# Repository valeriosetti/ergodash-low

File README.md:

# What's this?

I've worked the ErgoDash keyboard for a while and it felt quite good, but it was a bit too
high for me. So I decided to design my own version in order to make it thinner.
Here's what I did:

- have all switches PCB mounted.
- do not use acrylic frame and let the PCB sit directly on the desktop.
- use low profile Gateron switches (KS-27).

In addition:

- I also added some holes at the corners of the board in order to make it
tiltable/adjustable with some screw.
- I replaced some of the pinky keys with 2u keycaps because my pinky's accuracy
is not really great.

## Kicad preview

## Picture of the assembled board

# What's next?

I've been using this keyboard for more than a year now and I find it really
comfortable. There are still some improvements I would like to try though:

- make a new version with Kailh choch v1 keys in order to see if I can make
it even thinner than this.
- improve keys' position and perhaps also reduce the overall number:
    - central keys are not easily reachable with the index finger, so they
      might be lowered a bit in the layout.
    - 4 keys in the low-left row are too much (I currently have 2 Win-keys +
      Ctrl + Alt), so they can be reduced.

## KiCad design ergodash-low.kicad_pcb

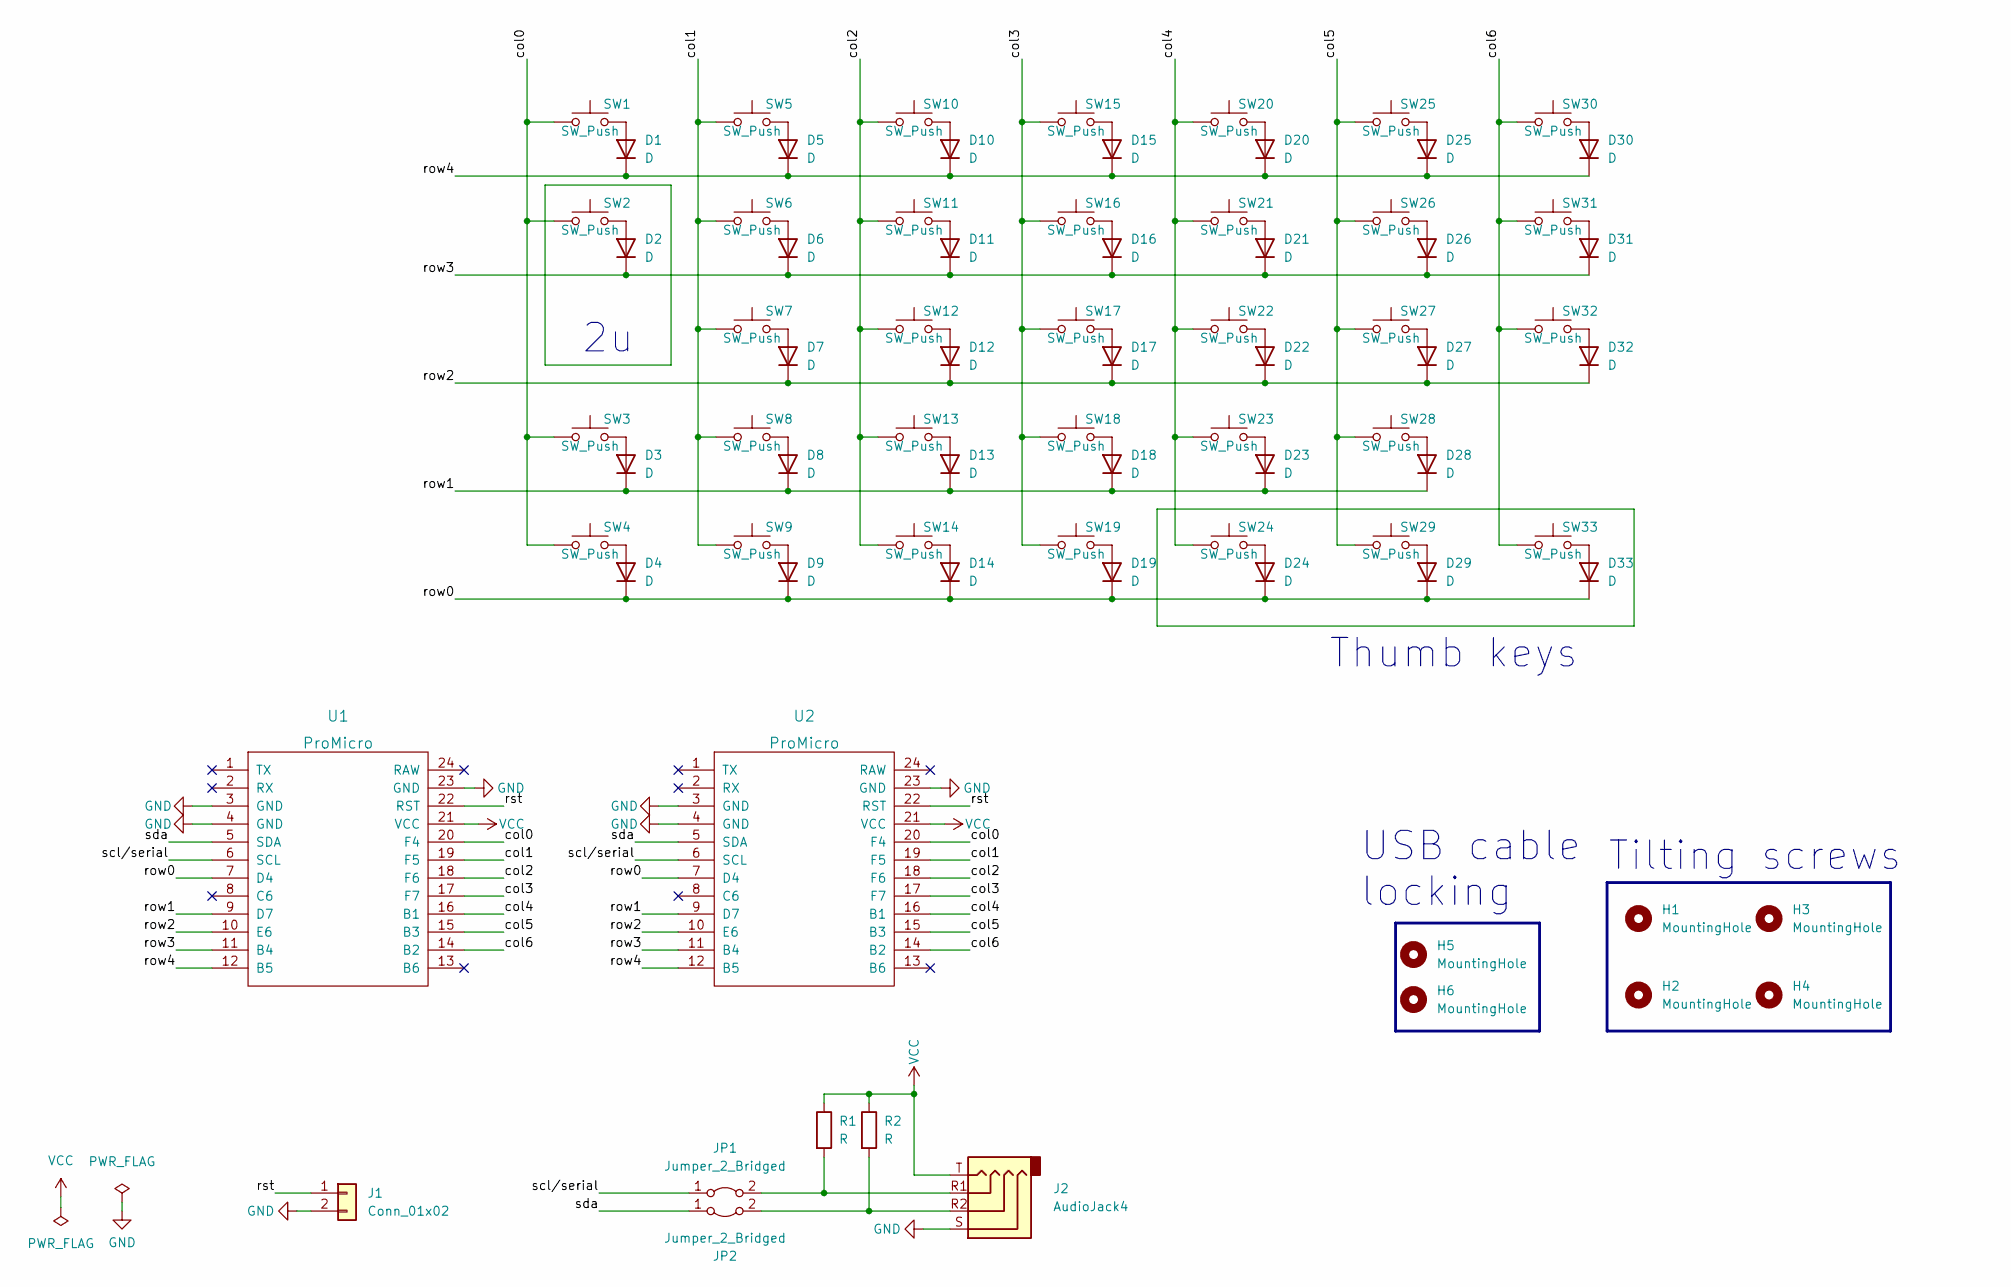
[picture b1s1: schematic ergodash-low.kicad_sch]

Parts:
D1, D2, D3, D4, D5, D6, D7, D8, D9, D10, D11, D12, D13, D14, D15, D16, D17, D18, D19, D20, D21, D22, D23, D24, D25, D26, D27, D28, D29, D30, D31, D32, D33: D; D_SOD-123-reversible
H1, H2, H3, H4: MountingHole; MountingHole_5.3mm_M5
H5, H6: MountingHole; MountingHole_4mm
J1: Conn_01x02; PinHeader_1x02_P2.54mm_Vertical
J2: AudioJack4; TRRS-PJ-320A-dual
JP1, JP2: Jumper_2_Bridged; SolderJumper-2_P1.3mm_Bridged_RoundedPad1.0x1.5mm
R1, R2: R; R_0603_1608Metric_Pad0.98x0.95mm_HandSolder
SW1, SW3, SW4, SW5, SW6, SW7, SW8, SW9, SW10, SW11, SW12, SW13, SW14, SW15, SW16, SW17, SW18, SW19, SW20, SW21, SW22, SW23, SW24, SW25, SW26, SW27, SW28, SW30, SW31, SW32: SW_Push; gateron_ks27_reversible
SW2, SW29, SW33: SW_Push; gateron_ks27_reversible_stabilizer
U1, U2: ProMicro

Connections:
/col0: SW1.1, SW2.1, SW3.1, SW4.1, U1.20 (F4), U2.20 (F4)
/col1: SW5.1, SW6.1, SW7.1, SW8.1, SW9.1, U1.19 (F5), U2.19 (F5)
/col2: SW10.1, SW11.1, SW12.1, SW13.1, SW14.1, U1.18 (F6), U2.18 (F6)
/col3: SW15.1, SW16.1, SW17.1, SW18.1, SW19.1, U1.17 (F7), U2.17 (F7)
/col4: SW20.1, SW21.1, SW22.1, SW23.1, SW24.1, U1.16 (B1), U2.16 (B1)
/col5: SW25.1, SW26.1, SW27.1, SW28.1, SW29.1, U1.15 (B3), U2.15 (B3)
/col6: SW30.1, SW31.1, SW32.1, SW33.1, U1.14 (B2), U2.14 (B2)
/row0: D4.1 (K), D9.1 (K), D14.1 (K), D19.1 (K), D24.1 (K), D29.1 (K), D33.1 (K), U1.7 (D4), U2.7 (D4)
/row1: D3.1 (K), D8.1 (K), D13.1 (K), D18.1 (K), D23.1 (K), D28.1 (K), U1.9 (D7), U2.9 (D7)
/row2: D7.1 (K), D12.1 (K), D17.1 (K), D22.1 (K), D27.1 (K), D32.1 (K), U1.10 (E6), U2.10 (E6)
/row3: D2.1 (K), D6.1 (K), D11.1 (K), D16.1 (K), D21.1 (K), D26.1 (K), D31.1 (K), U1.11 (B4), U2.11 (B4)
/row4: D1.1 (K), D5.1 (K), D10.1 (K), D15.1 (K), D20.1 (K), D25.1 (K), D30.1 (K), U1.12 (B5), U2.12 (B5)
/rst: J1.1, U1.22 (RST), U2.22 (RST)
/scl/serial: JP1.1 (A), U1.6 (SCL), U2.6 (SCL)
/sda: JP2.1 (A), U1.5 (SDA), U2.5 (SDA)
GND: J1.2, J2.S, U1.3 (GND), U1.4 (GND), U1.23 (GND), U2.3 (GND), U2.4 (GND), U2.23 (GND)
unnamed: D1.2 (A), SW1.2
unnamed: D2.2 (A), SW2.2
unnamed: D3.2 (A), SW3.2
unnamed: D4.2 (A), SW4.2
unnamed: D5.2 (A), SW5.2
unnamed: D6.2 (A), SW6.2
unnamed: D7.2 (A), SW7.2
unnamed: D8.2 (A), SW8.2
unnamed: D9.2 (A), SW9.2
unnamed: D10.2 (A), SW10.2
unnamed: D11.2 (A), SW11.2
unnamed: D12.2 (A), SW12.2
unnamed: D13.2 (A), SW13.2
unnamed: D14.2 (A), SW14.2
unnamed: D15.2 (A), SW15.2
unnamed: D16.2 (A), SW16.2
unnamed: D17.2 (A), SW17.2
unnamed: D18.2 (A), SW18.2
unnamed: D19.2 (A), SW19.2
unnamed: D20.2 (A), SW20.2
unnamed: D21.2 (A), SW21.2
unnamed: D22.2 (A), SW22.2
unnamed: D23.2 (A), SW23.2
unnamed: D24.2 (A), SW24.2
unnamed: D25.2 (A), SW25.2
unnamed: D26.2 (A), SW26.2
unnamed: D27.2 (A), SW27.2
unnamed: D28.2 (A), SW28.2
unnamed: D29.2 (A), SW29.2
unnamed: D30.2 (A), SW30.2
unnamed: D31.2 (A), SW31.2
unnamed: D32.2 (A), SW32.2
unnamed: D33.2 (A), SW33.2
unnamed: J2.R1, JP1.2 (B), R1.2
unnamed: J2.R2, JP2.2 (B), R2.2
VCC: J2.T, R1.1, R2.1, U1.21 (VCC), U2.21 (VCC)

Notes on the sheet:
USB cable locking
Tilting screws
Thumb keys

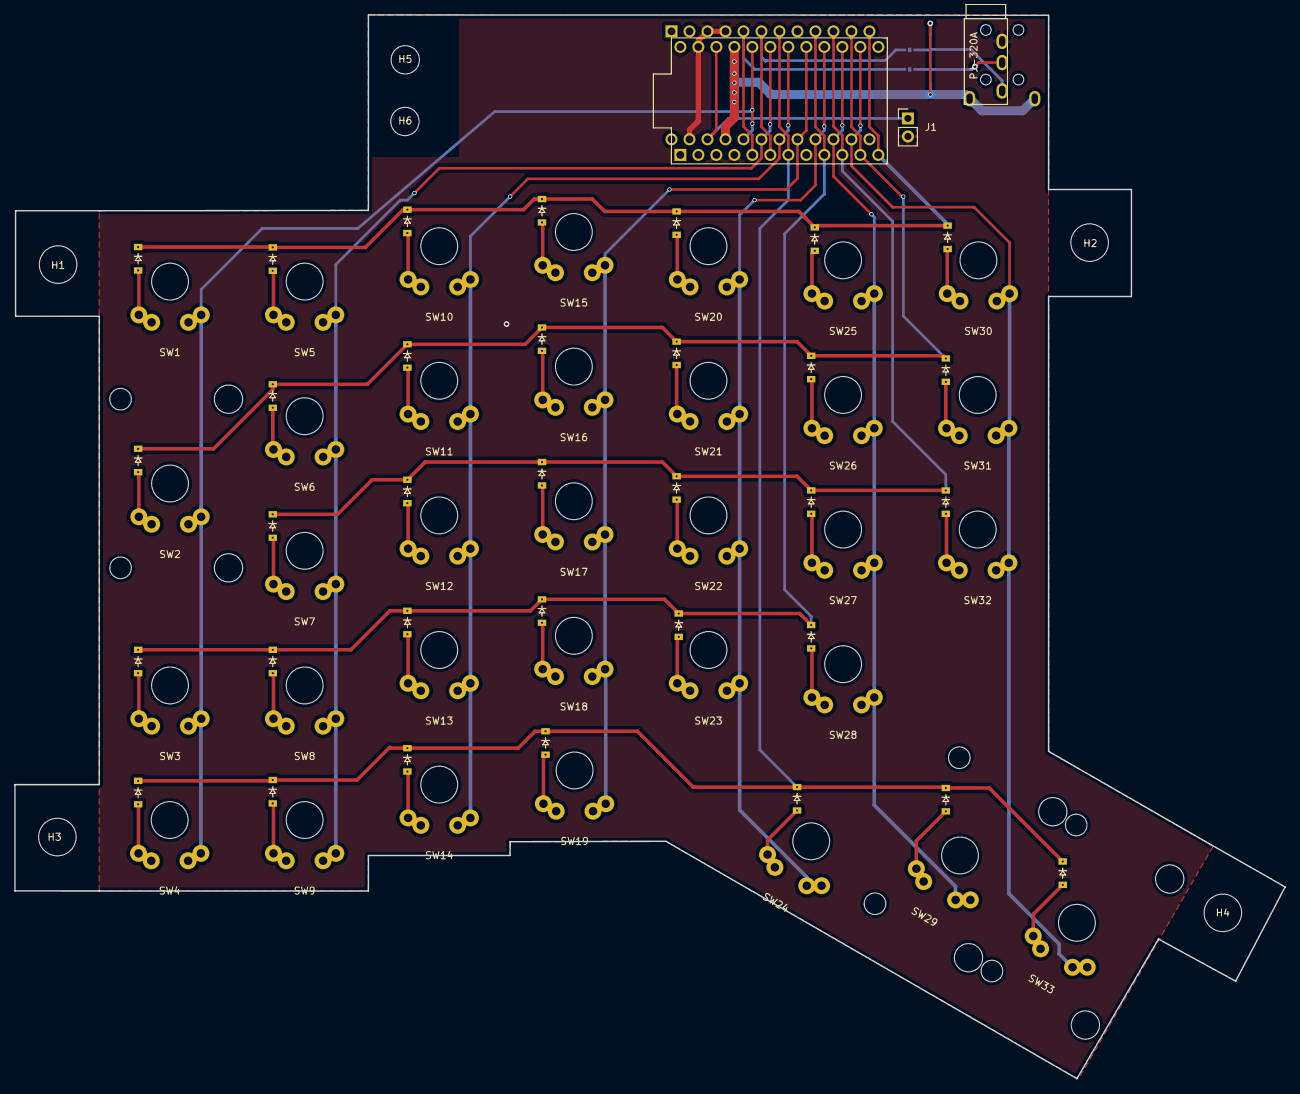
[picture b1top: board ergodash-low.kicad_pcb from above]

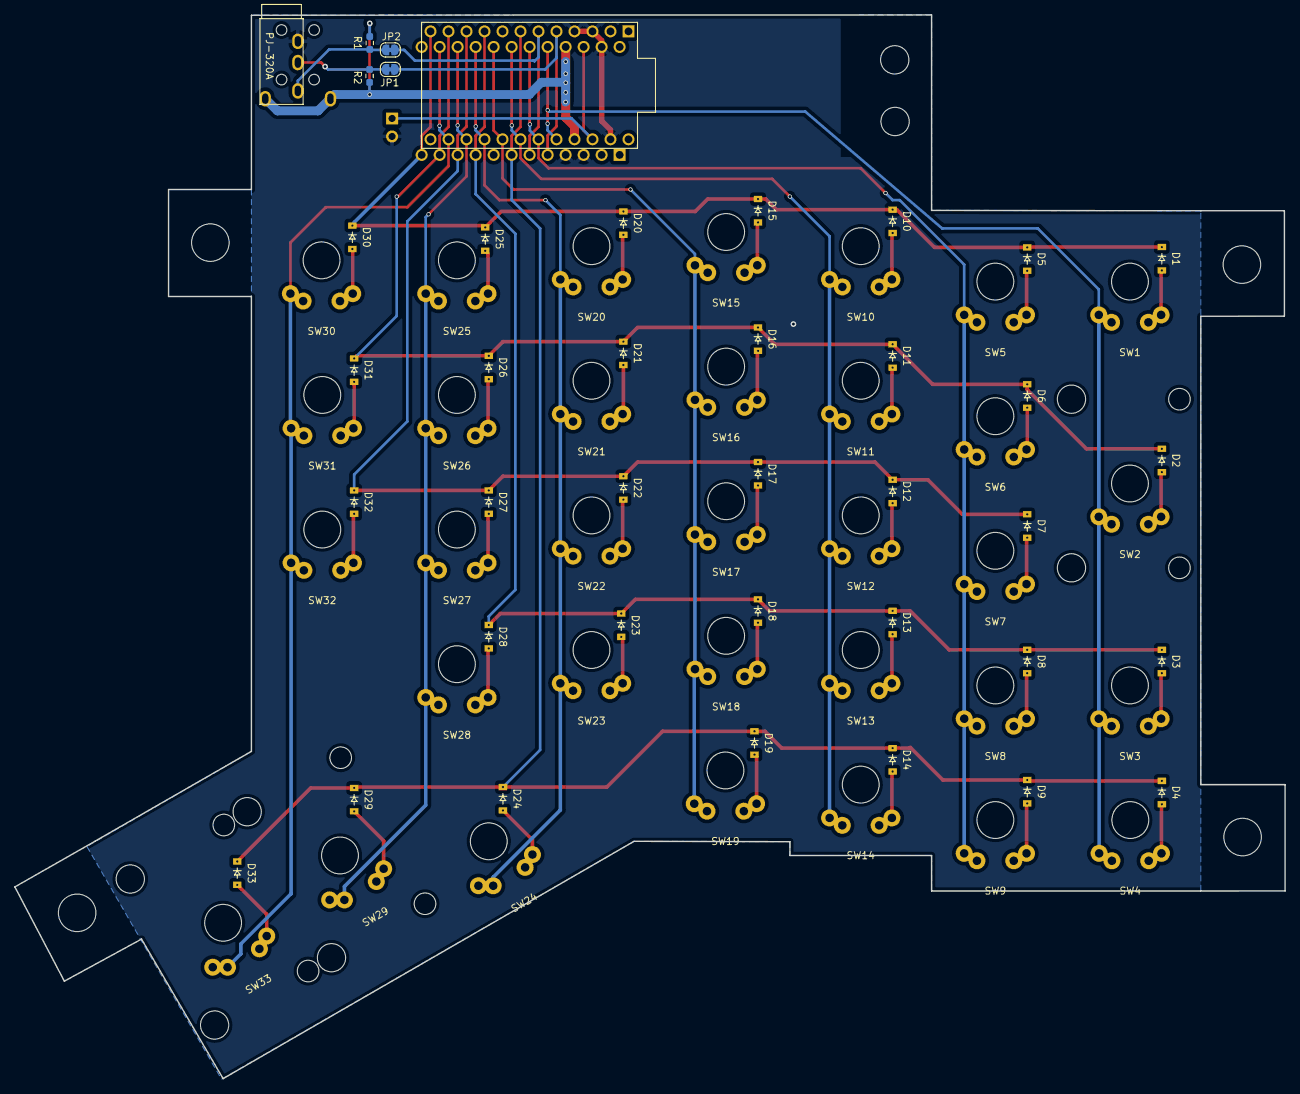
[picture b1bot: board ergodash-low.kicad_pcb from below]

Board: 2 copper layers, 179.3 x 150.1 mm, 80 parts (38 on the bottom side), 52 nets.

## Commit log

2023-03-28 adding ergogen source file and DXF
2023-03-28 adding local library - customizing existing components
2023-03-28 first version of schematic & pcb (to be finalized)
2023-03-28 adding images folder
2023-03-30 datasheet: added mech drawing for the Gateron KS27
2023-03-30 removed unused libraries and updated footprints
2023-03-30 completed schematic and pcb
2023-03-30 adding gerber files for jlcpcb
2023-03-30 updated image of the board
2024-07-30 add gateron KS27 + kailh choc v1 combo footprint
2024-07-30 readme: updated description
